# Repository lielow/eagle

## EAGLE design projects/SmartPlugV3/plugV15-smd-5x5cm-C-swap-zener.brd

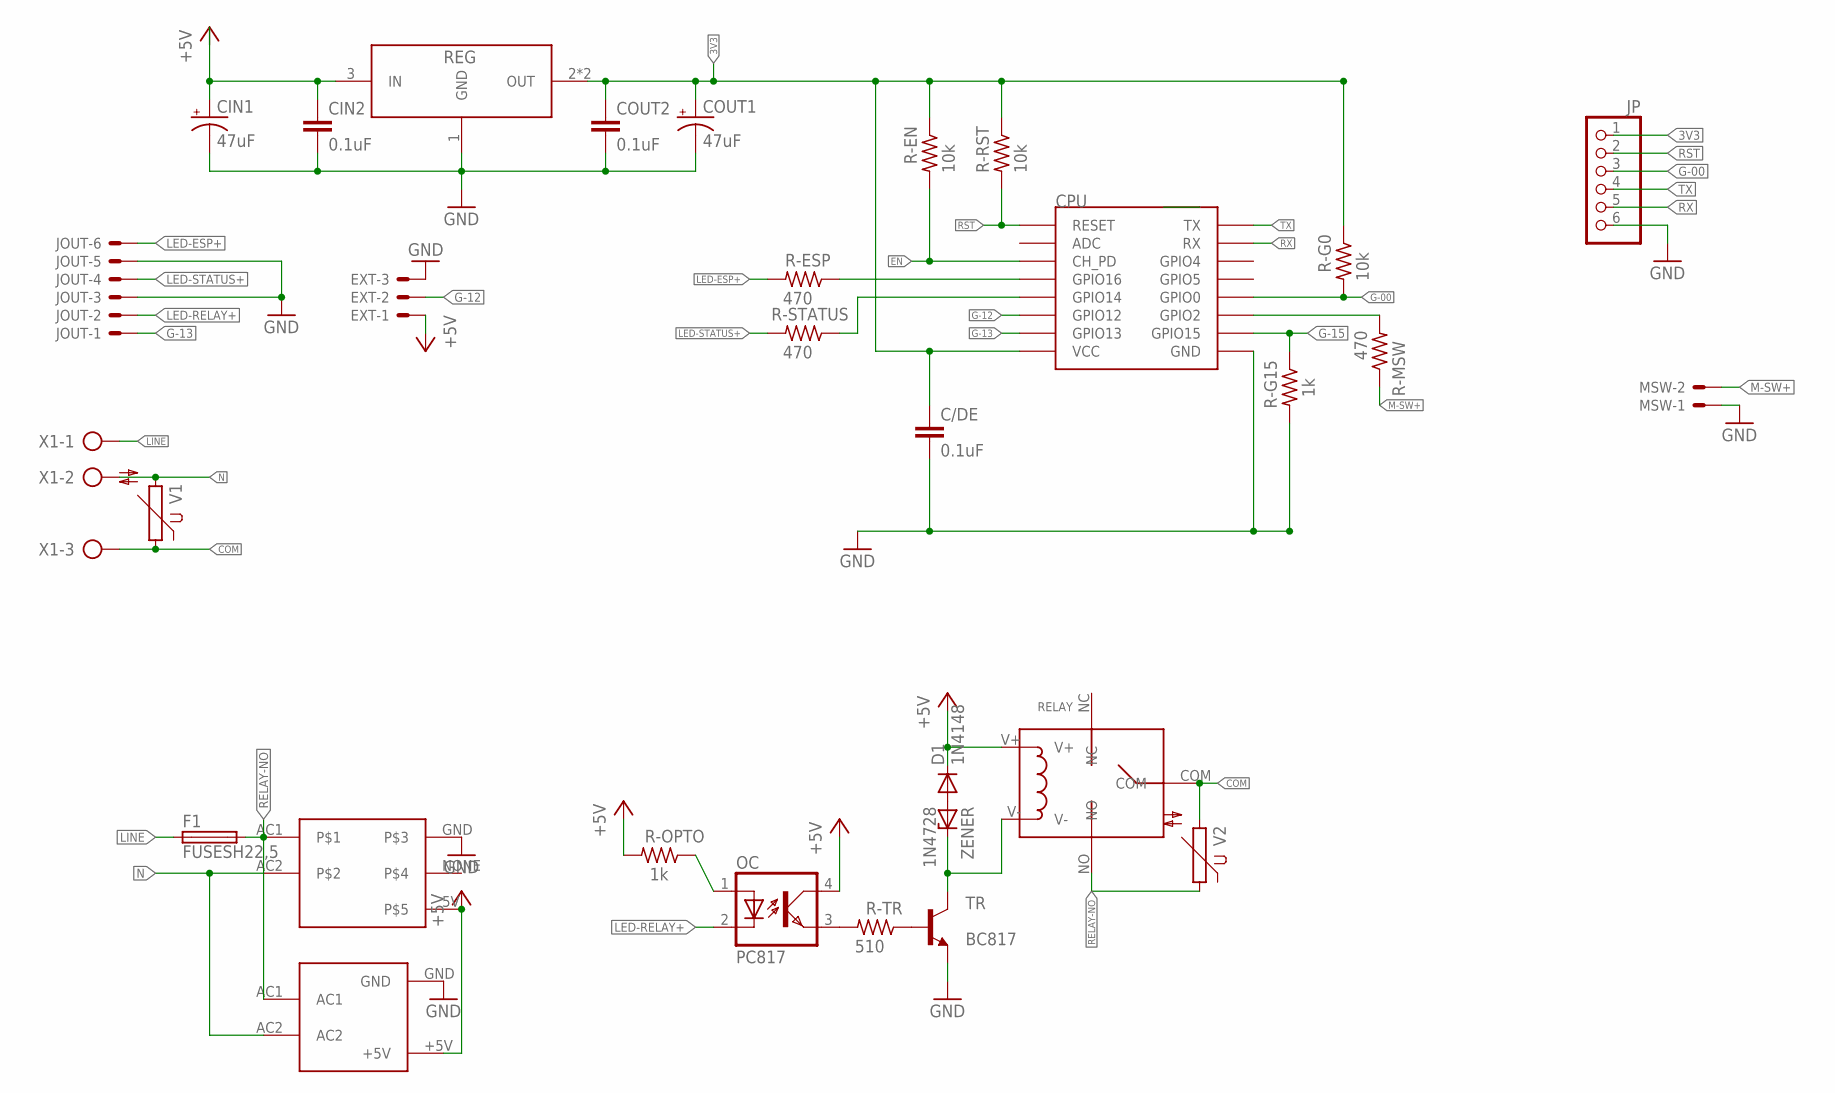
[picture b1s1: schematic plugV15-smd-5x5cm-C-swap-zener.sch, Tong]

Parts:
C/DE: 0.1uF; C0805
CIN1: 47uF; E2,5-5
CIN2: 0.1uF; C0805
COUT1: 47uF; E2,5-5
COUT2: 0.1uF; C0805
CPU: ESP12SMD; ESP12-SMD
D1: 1N4148; DO35-7
EXT: 53048-03
F1: FUSESH22,5; SH22,5
HLK: HLK-PM01
JOUT: 53048-06
JP: PINHD-1X6; 1X06
MSW: 53048-02
OC: PC817; DIL04
R-EN: 10k; M0805
R-ESP: 470; M0805
R-G0: 10k; M0805
R-G15: 1k; M0805
R-MSW: 470; M0805
R-OPTO: 1k; M0805
R-RST: 10k; M0805
R-STATUS: 470; M0805
R-TR: 510; M0805
REG: AMS1117-3.3; SOT-223
RELAY: RELAY-SONGLE
TR: BC817; SOT23-BEC
U$4: POWERSUPPLY-5V-700MA
V1, V2: S14K11
X1: AK300/3
ZENER: 1N4728; DO41Z10

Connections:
3V3: C/DE.1, COUT1.+, COUT2.1, CPU.VCC, JP.1, R-EN.1, R-G0.1, R-RST.1, REG.2 (OUT), REG.4 (OUT)
+5V: CIN1.+, CIN2.1, D1.C, EXT.1, HLK.+5V, OC.4 (COL), R-OPTO.2, REG.3 (IN), RELAY.V+, U$4.5V
COM: RELAY.COM, V1.1, V2.2, X1.3
EN: CPU.CH_PD, R-EN.2
G-00: CPU.GPIO0, JP.3, R-G0.2
G-12: CPU.GPIO12, EXT.2
G-13: CPU.GPIO13, JOUT.1
G-15: CPU.GPIO15, R-G15.1
GND: C/DE.2, CIN1.-, CIN2.2, COUT1.-, COUT2.2, CPU.GND, EXT.3, HLK.GND, JOUT.3, JOUT.5, JP.6, MSW.1, R-G15.2, REG.1 (GND), TR.E, U$4.GND
LED-ESP+: JOUT.6, R-ESP.2
LED-RELAY+: JOUT.2, OC.2 (C)
LED-STATUS+: JOUT.4, R-STATUS.2
LINE: F1.1, X1.1
M-SW+: MSW.2, R-MSW.1
N: HLK.AC2, U$4.AC2, V1.2, X1.2
unnamed: OC.3 (EMIT), R-TR.2
unnamed: R-TR.1, TR.B
unnamed: CPU.GPIO2, R-MSW.2
unnamed: CPU.GPIO14, R-STATUS.1
unnamed: OC.1 (A), R-OPTO.1
unnamed: D1.A, ZENER.A
unnamed: RELAY.V-, TR.C, ZENER.C
unnamed: CPU.GPIO16, R-ESP.1
RELAY-NO: F1.2, HLK.AC1, RELAY.NO, U$4.AC1, V2.1
RST: CPU.RESET, JP.2, R-RST.2
RX: CPU.RXD0 (RX), JP.5
TX: CPU.TXD0 (TX), JP.4

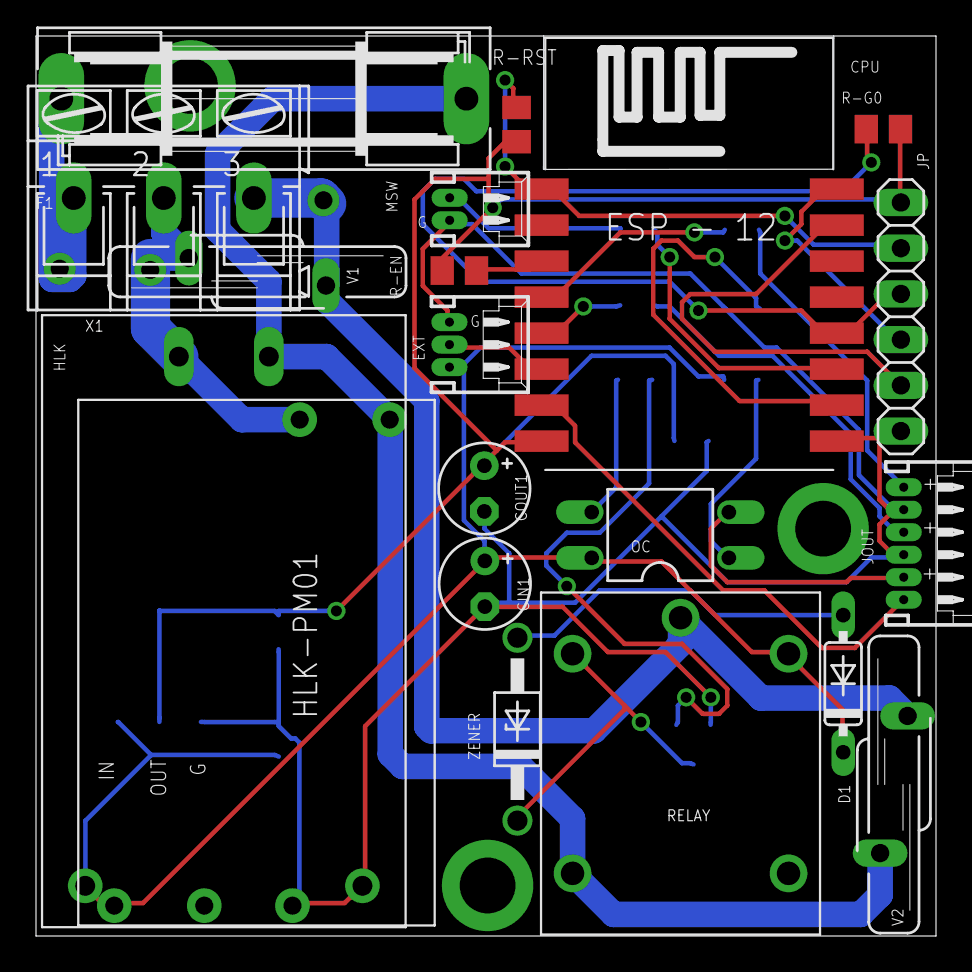
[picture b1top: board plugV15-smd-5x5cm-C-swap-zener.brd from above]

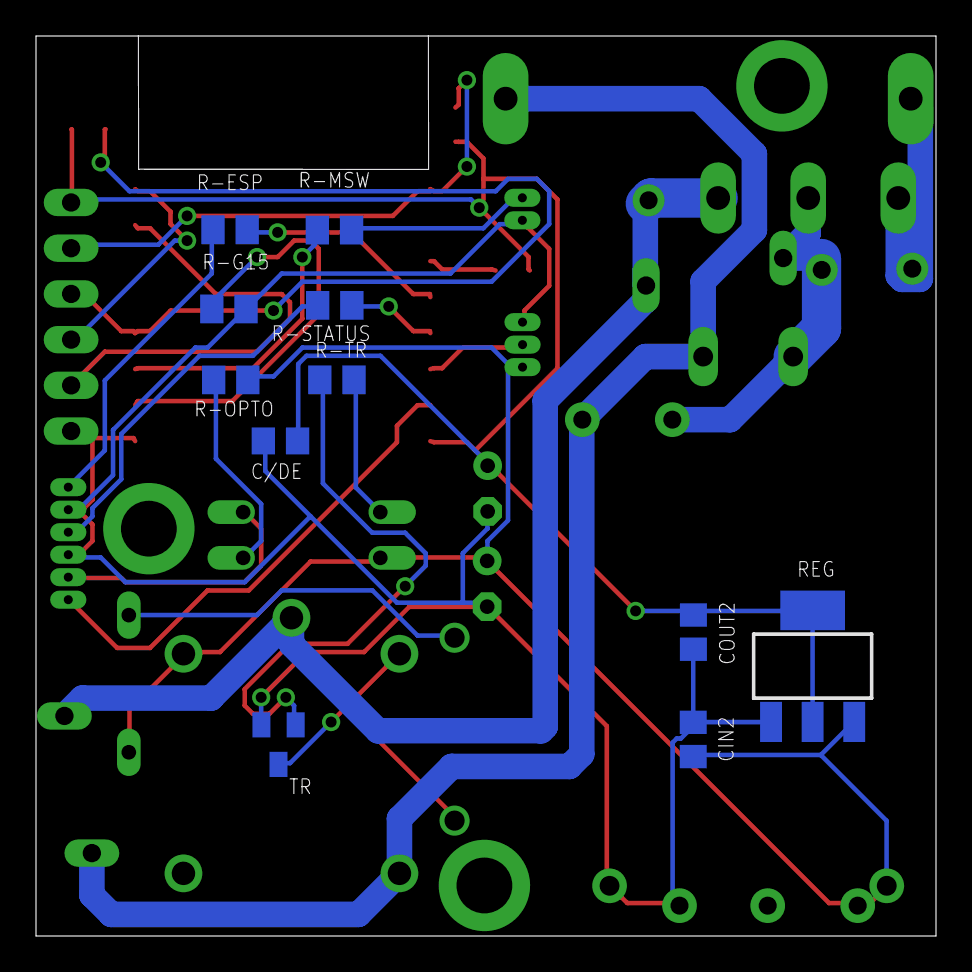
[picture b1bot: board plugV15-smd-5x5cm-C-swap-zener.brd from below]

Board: 2 copper layers, 50.0 x 50.0 mm, 31 parts (11 on the bottom side), 27 nets.

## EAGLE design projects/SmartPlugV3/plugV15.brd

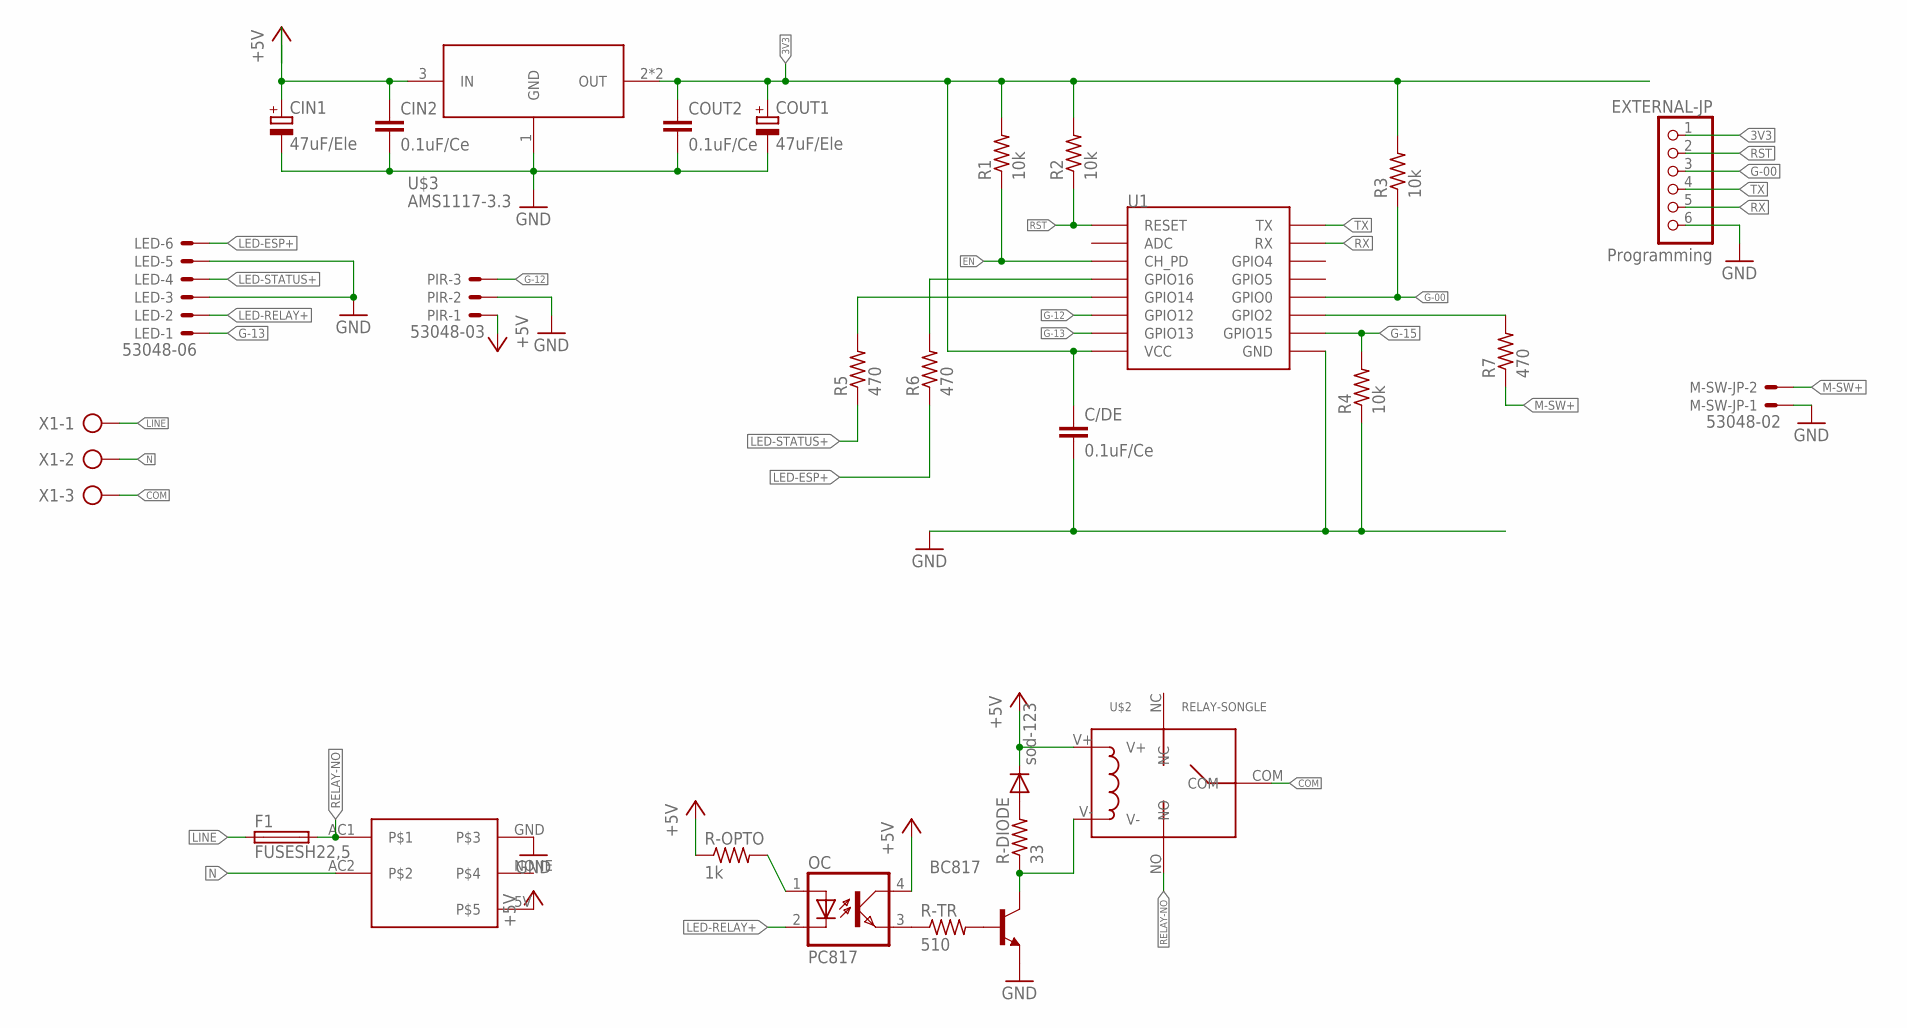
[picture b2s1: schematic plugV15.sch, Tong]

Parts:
1N4148: sod-123; SOD-123_MINI-SMA
BC817: BC817-NPN-SOT23-BEC; SOT23-BEC
C/DE: 0.1uF/Ce; C0805
CIN1: 47uF/Ele; E2-5
CIN2: 0.1uF/Ce; C0805
COUT1: 47uF/Ele; E2-5
COUT2: 0.1uF/Ce; C0805
EXTERNAL-JP: Programming; 1X06
F1: FUSESH22,5; SH22,5
LED: 53048-06
M-SW-JP: 53048-02
OC: PC817; DIL04
PIR: 53048-03
R1, R2, R3, R4: 10k; 0207/10
R5, R6, R7: 470; 0207/10
R-DIODE: 33; R0805
R-OPTO: 1k; R0805
R-TR: 510; R0805
U1: ESP12SMD; ESP12-SMD
U$2: RELAY-SONGLE
U$3: AMS1117-3.3; SOT-223
U$4: POWERSUPPLY-5V-700MA
X1: AK300/3

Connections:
3V3: C/DE.1, COUT1.+, COUT2.1, EXTERNAL-JP.1, R1.2, R2.2, R3.2, U1.VCC, U$3.2 (OUT), U$3.4 (OUT)
+5V: 1N4148.C, CIN1.+, CIN2.1, OC.4 (COL), PIR.1, R-OPTO.1, U$2.V+, U$3.3 (IN), U$4.5V
COM: U$2.COM, X1.3
EN: R1.1, U1.CH_PD
G-00: EXTERNAL-JP.3, R3.1, U1.GPIO0
G-12: PIR.3, U1.GPIO12
G-13: LED.1, U1.GPIO13
G-15: R4.2, U1.GPIO15
GND: BC817.E, C/DE.2, CIN1.-, CIN2.2, COUT1.-, COUT2.2, EXTERNAL-JP.6, LED.3, LED.5, M-SW-JP.1, PIR.2, R4.1, U1.GND, U$3.1 (GND), U$4.GND
LED-ESP+: LED.6, R6.1
LED-RELAY+: LED.2, OC.2 (C)
LED-STATUS+: LED.4, R5.1
LINE: F1.1, X1.1
M-SW+: M-SW-JP.2, R7.1
N: U$4.AC2, X1.2
unnamed: OC.3 (EMIT), R-TR.1
unnamed: BC817.B, R-TR.2
unnamed: R6.2, U1.GPIO16
unnamed: R7.2, U1.GPIO2
unnamed: R5.2, U1.GPIO14
unnamed: OC.1 (A), R-OPTO.2
unnamed: 1N4148.A, R-DIODE.2
unnamed: BC817.C, R-DIODE.1, U$2.V-
RELAY-NO: F1.2, U$2.NO, U$4.AC1
RST: EXTERNAL-JP.2, R2.1, U1.RESET
RX: EXTERNAL-JP.5, U1.RXD0 (RX)
TX: EXTERNAL-JP.4, U1.TXD0 (TX)

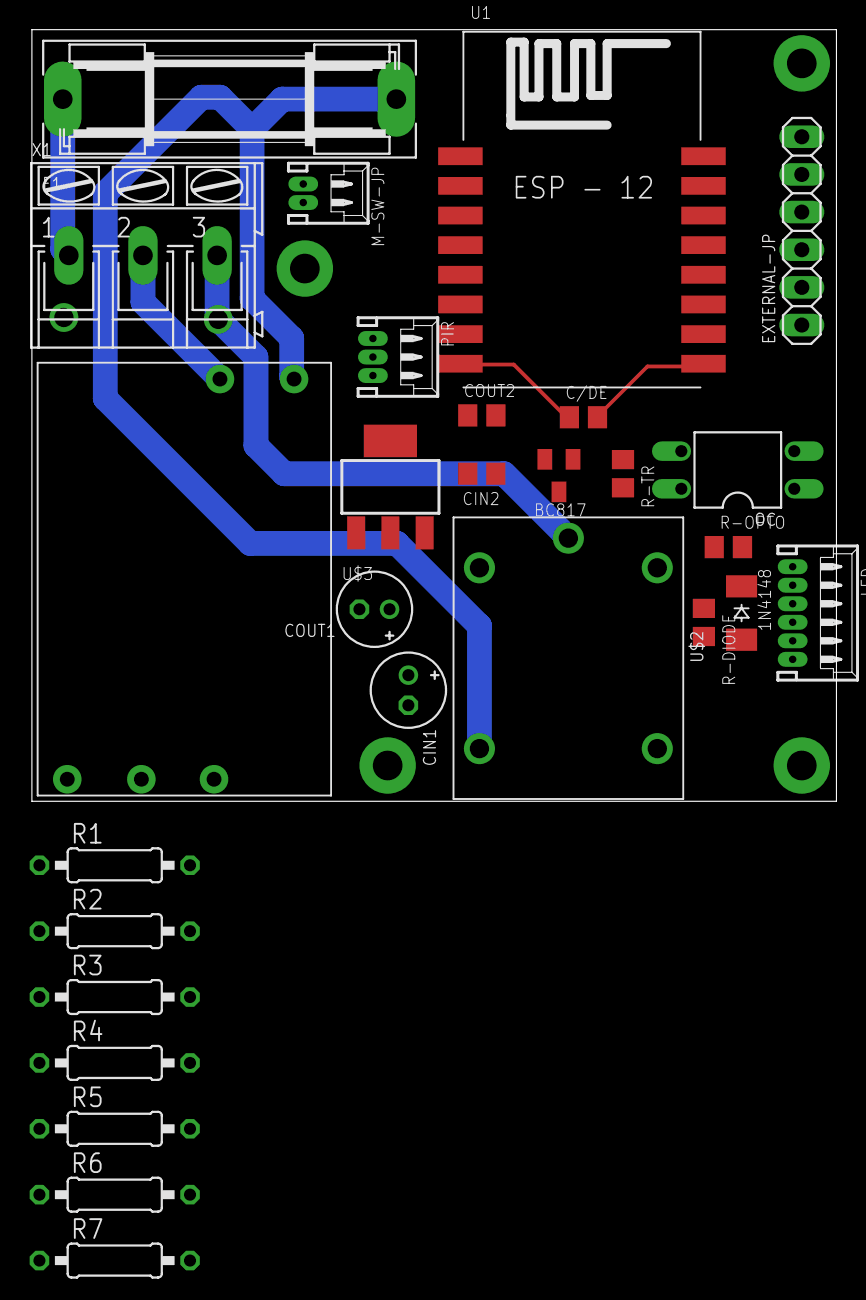
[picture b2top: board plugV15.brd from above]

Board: 2 copper layers, 54.3 x 52.1 mm, 28 parts (0 on the bottom side), 27 nets.

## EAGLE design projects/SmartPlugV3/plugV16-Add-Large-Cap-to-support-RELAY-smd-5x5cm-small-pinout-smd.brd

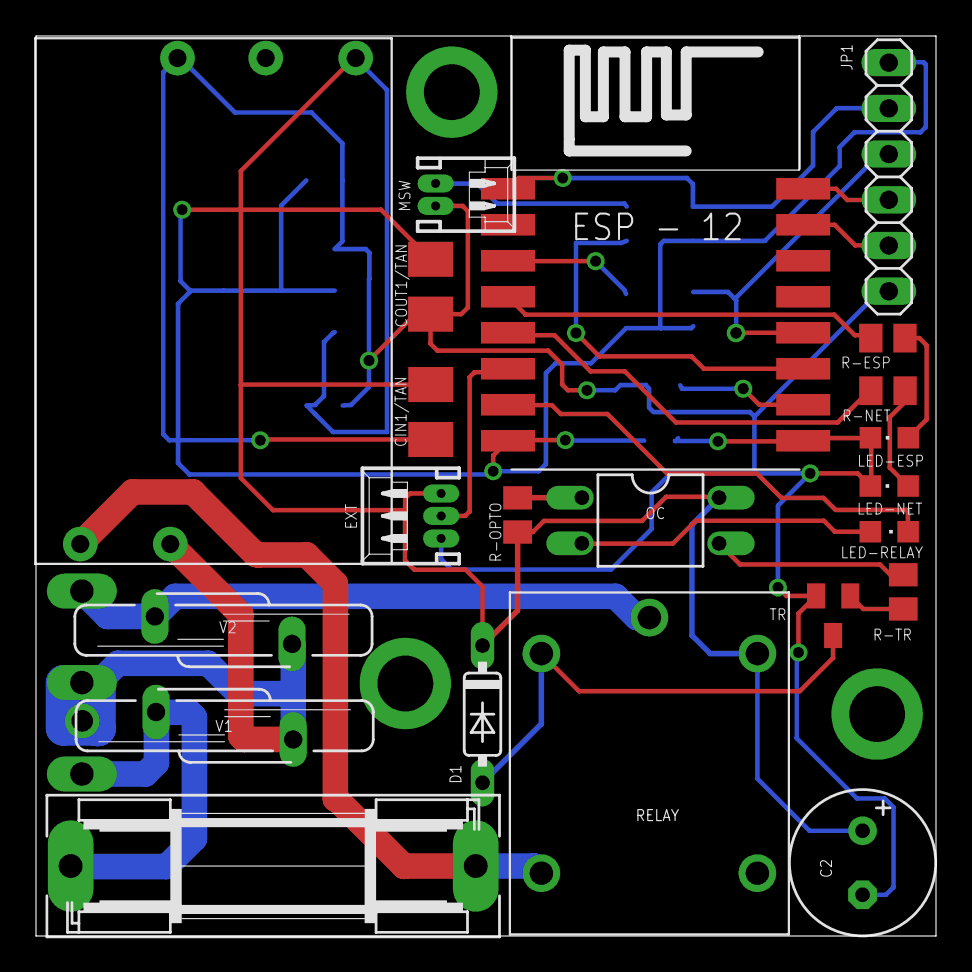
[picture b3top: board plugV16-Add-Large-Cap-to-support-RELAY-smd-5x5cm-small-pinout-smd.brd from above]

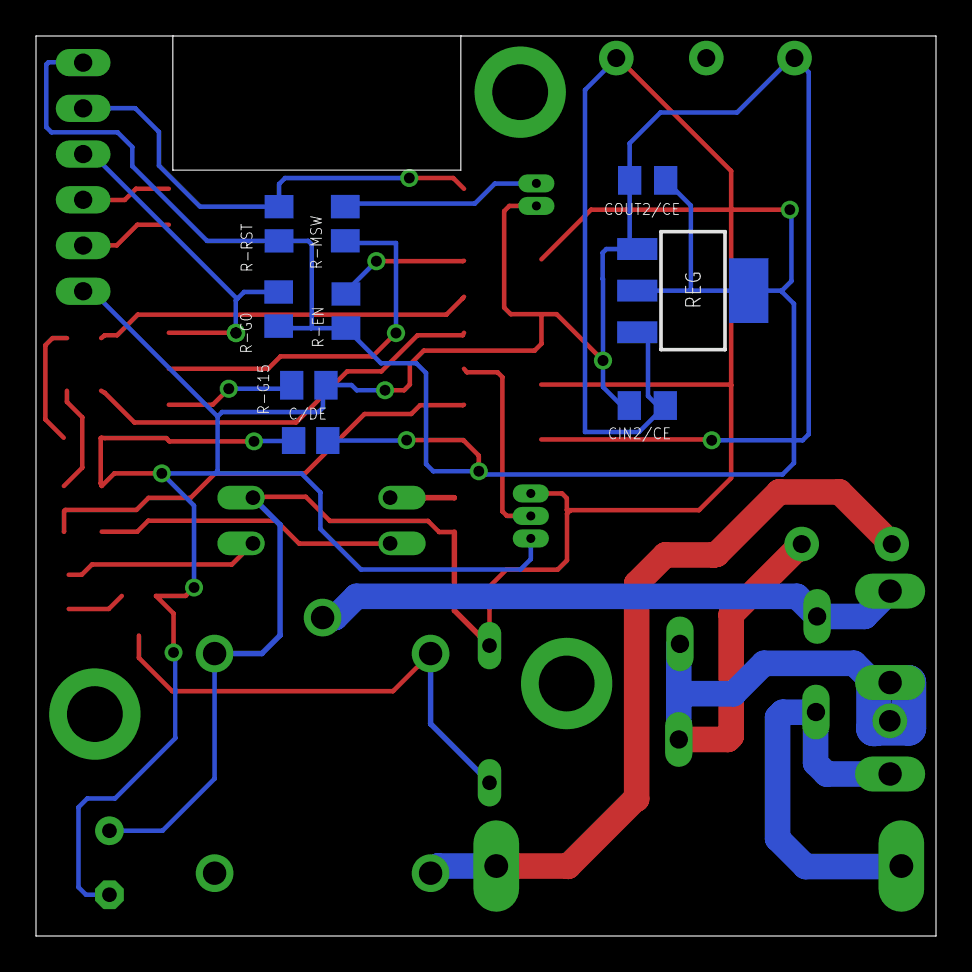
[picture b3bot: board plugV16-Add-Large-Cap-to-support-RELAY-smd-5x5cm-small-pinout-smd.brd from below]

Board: 2 copper layers, 50.0 x 50.0 mm, 32 parts (9 on the bottom side), 26 nets.

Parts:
C2: 470-1000uF; E3,5-8
C/DE: 0.1uF; C0805
CIN1/TAN: 22uF; B/3528-21R
CIN2/CE: 0.1uF; C0805K
COUT1/TAN: 22uF; B/3528-21R
COUT2/CE: 0.1uF; C0805K
CPU: ESP12-SMD
D1: 1N4148; DO35-7
EXT: 53048-03
F1: FUSESH22,5; SH22,5
JP1: 1X06
LED-ESP: CHIPLED_0805
LED-NET: CHIPLED_0805
LED-RELAY: CHIPLED_0805
MSW: 53048-02
OC: PC817; DIL04
R-EN: 10k; M0805
R-ESP: 470; M0805
R-G0: 10k; M0805
R-G15: 1k; M0805
R-MSW: 470; M0805
R-NET: 470; M0805
R-OPTO: 1k; M0805
R-RST: 10k; M0805
R-TR: 510; M0805
REG: SOT-223
RELAY: RELAY-SONGLE
TR: BC817; SOT23-BEC
U$1: POWER-RELAY-FOOTPRINT
U$4: POWERSUPPLY-5V-700MA
V1, V2: S14K11

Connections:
3V3: C/DE.1, COUT1/TAN.+, COUT2/CE.1, CPU.VCC, JP1.6, R-EN.1, R-G0.1, R-RST.1, REG.2, REG.4
+5V: C2.+, CIN1/TAN.+, CIN2/CE.1, D1.C, EXT.1, OC.4, R-OPTO.2, REG.3, RELAY.V+, U$4.5V
EN: CPU.CH_PD, R-EN.2
G-00: CPU.GPIO0, JP1.4, R-G0.2
G-12: CPU.GPIO12, EXT.2
G-13: CPU.GPIO13, LED-RELAY.C
G-15: CPU.GPIO15, R-G15.1
GND: C2.-, C/DE.2, CIN1/TAN.-, CIN2/CE.2, COUT1/TAN.-, COUT2/CE.2, CPU.GND, EXT.3, JP1.1, LED-ESP.C, LED-NET.C, MSW.1, R-G15.2, REG.1, TR.E, U$4.GND
LINE: F1.1, U$1.LINE, V1.2
M-SW+: MSW.2, R-MSW.1
N: U$1.COMMON, U$4.AC2, V1.1, V2.2
unnamed: OC.3, R-TR.2
unnamed: R-TR.1, TR.B
unnamed: LED-ESP.A, R-ESP.2
unnamed: CPU.GPIO2, R-MSW.2
unnamed: CPU.GPIO14, R-NET.1
unnamed: OC.1, R-OPTO.1
unnamed: LED-NET.A, R-NET.2
unnamed: D1.A, RELAY.V-, TR.C
unnamed: CPU.GPIO16, R-ESP.1
unnamed: LED-RELAY.A, OC.2
RELAY-COM: RELAY.COM, U$1.RELAY, V2.1
RELAY-NO: F1.2, RELAY.NO, U$4.AC1
RST: CPU.RESET, JP1.5, R-RST.2
RX: CPU.RXD0, JP1.2
TX: CPU.TXD0, JP1.3

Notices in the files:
parts and their libraries:
SparkFun-Aesthetics: Licensing: Creative Commons ShareAlike 4.0 International - https://creativecommons.org/licenses/by-sa/4.0
